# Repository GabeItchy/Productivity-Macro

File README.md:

# Productivity Macro
 macropad for blender and whatever.

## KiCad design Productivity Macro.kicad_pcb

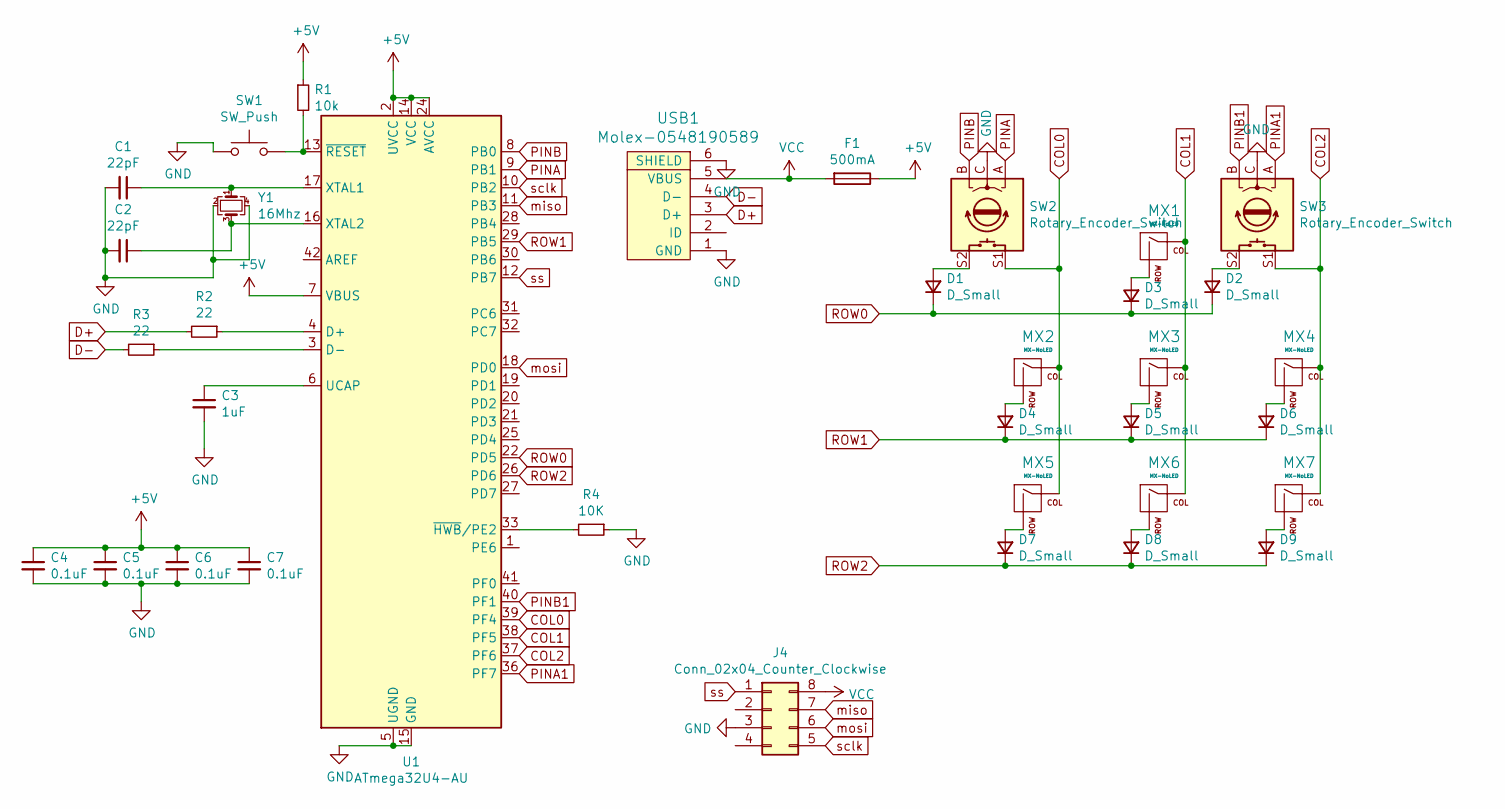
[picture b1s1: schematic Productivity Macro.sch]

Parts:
C1, C2: 22pF; C_0805_2012Metric
C3: 1uF; C_0805_2012Metric
C4, C5, C6: 0.1uF; C_0805_2012Metric
C7: 0.1uF; D_SOD-123
D1, D2, D3, D4, D5, D6, D7, D8, D9: D_Small; D_SOD-123
F1: 500mA; Fuse_1206_3216Metric
J4: Conn_02x04_Counter_Clockwise; PinSocket_2x04_P2.00mm_Vertical
MX1, MX2, MX3, MX4, MX5, MX6, MX7: MX-NoLED; MX-1U-NoLED
R1: 10k; R_0805_2012Metric
R2, R3: 22; R_0805_2012Metric
R4: 10K; R_0805_2012Metric
SW1: SW_Push; SKQG-1155865
SW2, SW3: Rotary_Encoder_Switch; RotaryEncoder_Alps_EC11E-Switch_Vertical_H20mm
U1: ATmega32U4-AU; TQFP-44_10x10mm_P0.8mm
USB1: Molex-0548190589
Y1: 16Mhz; Crystal_SMD_3225-4Pin_3.2x2.5mm

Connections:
+5V: C4.1, C5.1, C6.1, C7.1, F1.1, R1.1, U1.2 (UVCC), U1.7 (VBUS), U1.14 (VCC), U1.24 (AVCC), U1.34 (VCC), U1.44 (AVCC)
COL0: MX2.1 (COL), MX5.1 (COL), SW2.S1, U1.39 (PF4)
COL1: MX1.1 (COL), MX3.1 (COL), MX6.1 (COL), U1.38 (PF5)
COL2: MX4.1 (COL), MX7.1 (COL), SW3.S1, U1.37 (PF6)
D+: R2.2, USB1.3 (D+)
D-: R3.2, USB1.4 (D-)
GND: C1.2, C2.2, C3.2, C4.2, C5.2, C6.2, C7.2, J4.3, R4.1, SW1.1, SW2.C, SW3.C, U1.5 (UGND), U1.15 (GND), U1.23 (GND), U1.35 (GND), U1.43 (GND), USB1.1 (GND), USB1.6 (SHIELD), Y1.2, Y1.4
unnamed: C1.1, U1.17 (XTAL1), Y1.1
unnamed: C2.1, U1.16 (XTAL2), Y1.3
unnamed: C3.1, U1.6 (UCAP)
unnamed: D1.2 (A), SW2.S2
unnamed: D2.2 (A), SW3.S2
unnamed: D3.2 (A), MX1.2 (ROW)
unnamed: D4.2 (A), MX2.2 (ROW)
unnamed: D5.2 (A), MX3.2 (ROW)
unnamed: D6.2 (A), MX4.2 (ROW)
unnamed: D7.2 (A), MX5.2 (ROW)
unnamed: D8.2 (A), MX6.2 (ROW)
unnamed: D9.2 (A), MX7.2 (ROW)
unnamed: R1.2, SW1.2, U1.13 (~RESET)
unnamed: R2.1, U1.4 (D+)
unnamed: R3.1, U1.3 (D-)
unnamed: R4.2, U1.33 (~HWB~/PE2)
PINA: SW2.A, U1.9 (PB1)
PINA1: SW3.A, U1.36 (PF7)
PINB: SW2.B, U1.8 (PB0)
PINB1: SW3.B, U1.40 (PF1)
ROW0: D1.1 (K), D2.1 (K), D3.1 (K), U1.22 (PD5)
ROW1: D4.1 (K), D5.1 (K), D6.1 (K), U1.29 (PB5)
ROW2: D7.1 (K), D8.1 (K), D9.1 (K), U1.26 (PD6)
VCC: F1.2, J4.8, USB1.5 (VBUS)
miso: J4.7, U1.11 (PB3)
mosi: J4.6, U1.18 (PD0)
sclk: J4.5, U1.10 (PB2)
ss: J4.1, U1.12 (PB7)

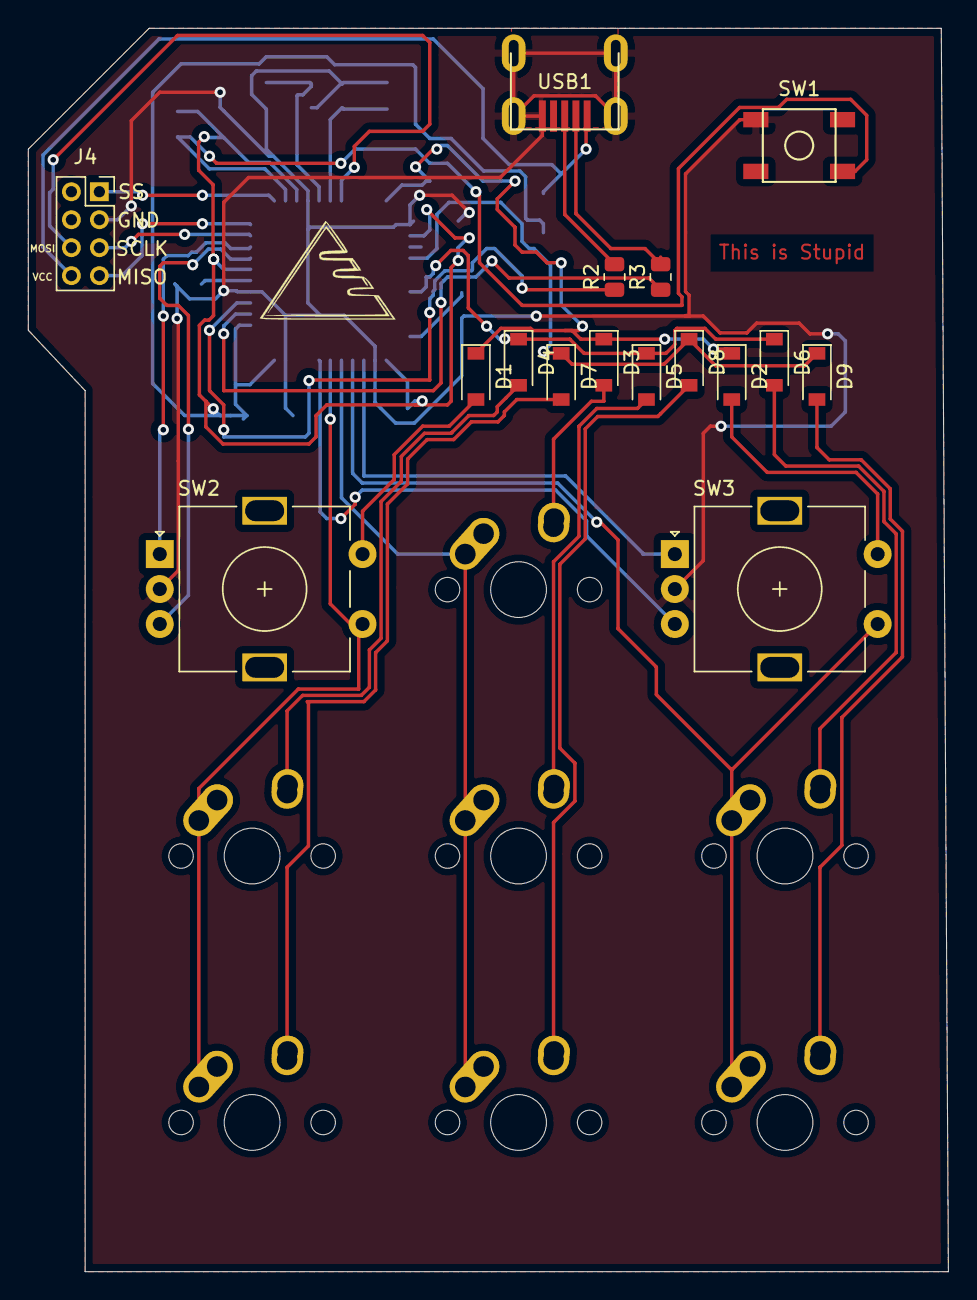
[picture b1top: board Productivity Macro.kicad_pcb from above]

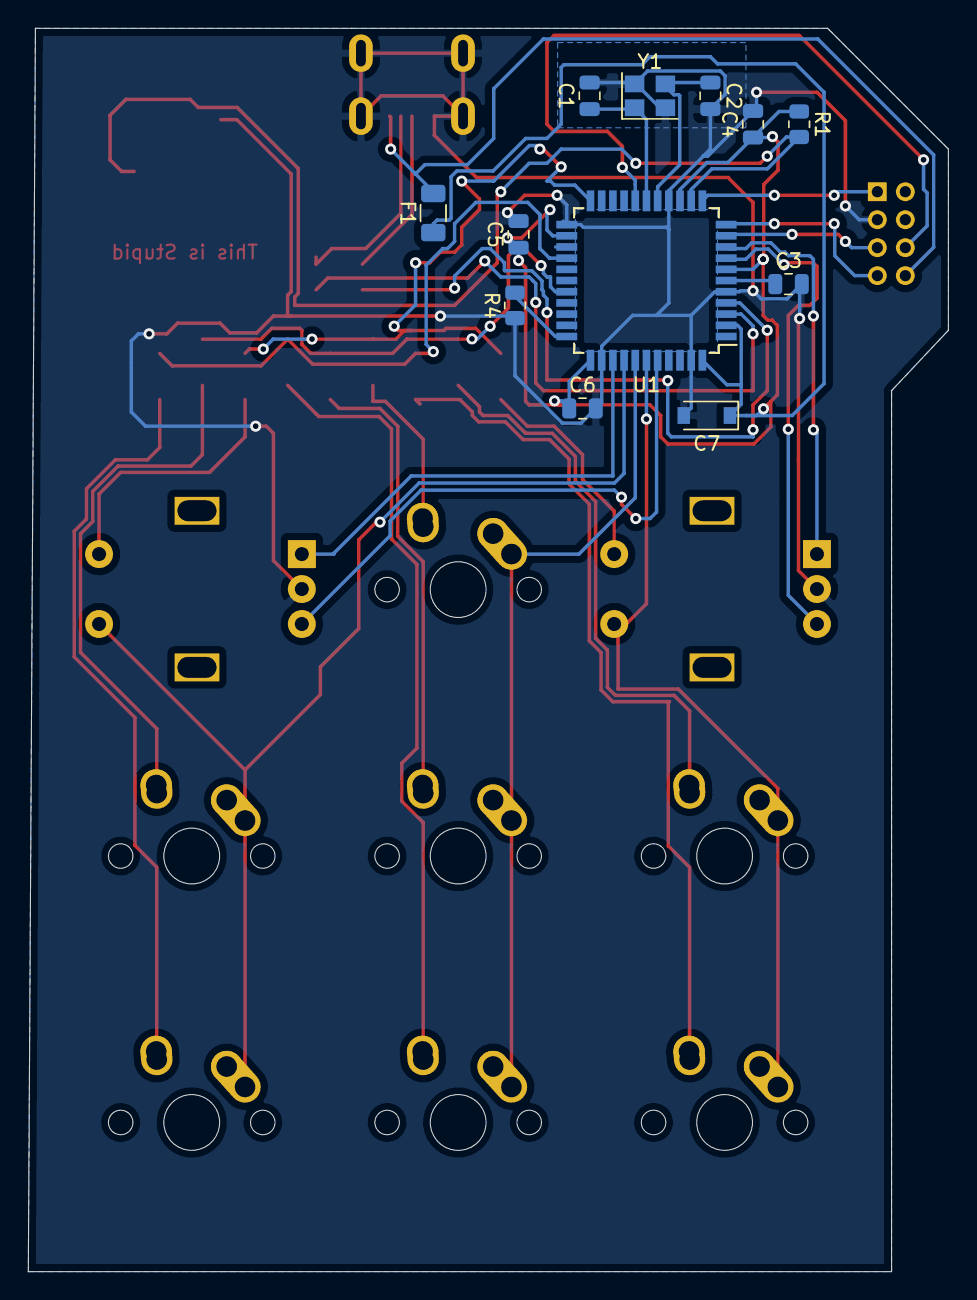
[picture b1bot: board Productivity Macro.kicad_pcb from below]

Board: 2 copper layers, 65.8 x 88.9 mm, 35 parts (12 on the bottom side), 35 nets.

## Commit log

2021-04-26 Added PCB and SCH
2021-04-26 https://github.com/ai03-2725/random-keyboard-parts.pretty
2021-04-26 Add footprint libraries
2021-04-26 rotary go spinnnnn
2021-04-26 hjhjhjh
2021-04-26 asdfgh
2021-04-26 klfg;;fkdlgdfgkl;kdfgl;
2021-04-26 process
2021-04-26 this is stupid
2021-04-27 close
2021-04-27 its done
2021-04-28 asasa
2021-04-28 dfsdfsdff
2021-06-05 time to get shit done again wooooo
2021-06-05 The beginning of the trackball
2021-06-06 Finished The Final Result
    Gerbers and everything :DD
2021-06-12 revamp
2022-02-02 jlkjlk
